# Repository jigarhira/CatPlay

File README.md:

# CatPlay
#### Device that allows you to play with your cat from anywhere.
CatPlay is a system comprised of an adjustable laser module and a live video stream. The user is shown a live video stream and can use controls on their mobile device to manipulate the laser pointer and play with the cat.

## Hardware
Laser Module is mounted on two servo motors to adjust laser position. Camera module is used to capture live stream. All components are connected to a Raspberry Pi Zero W which hosts the web server for the application.

## Software
When a client connects to the web server, they are provided with a video stream and control buttons to manipulate the laser in real time.

#
#### (project is a work in progress)

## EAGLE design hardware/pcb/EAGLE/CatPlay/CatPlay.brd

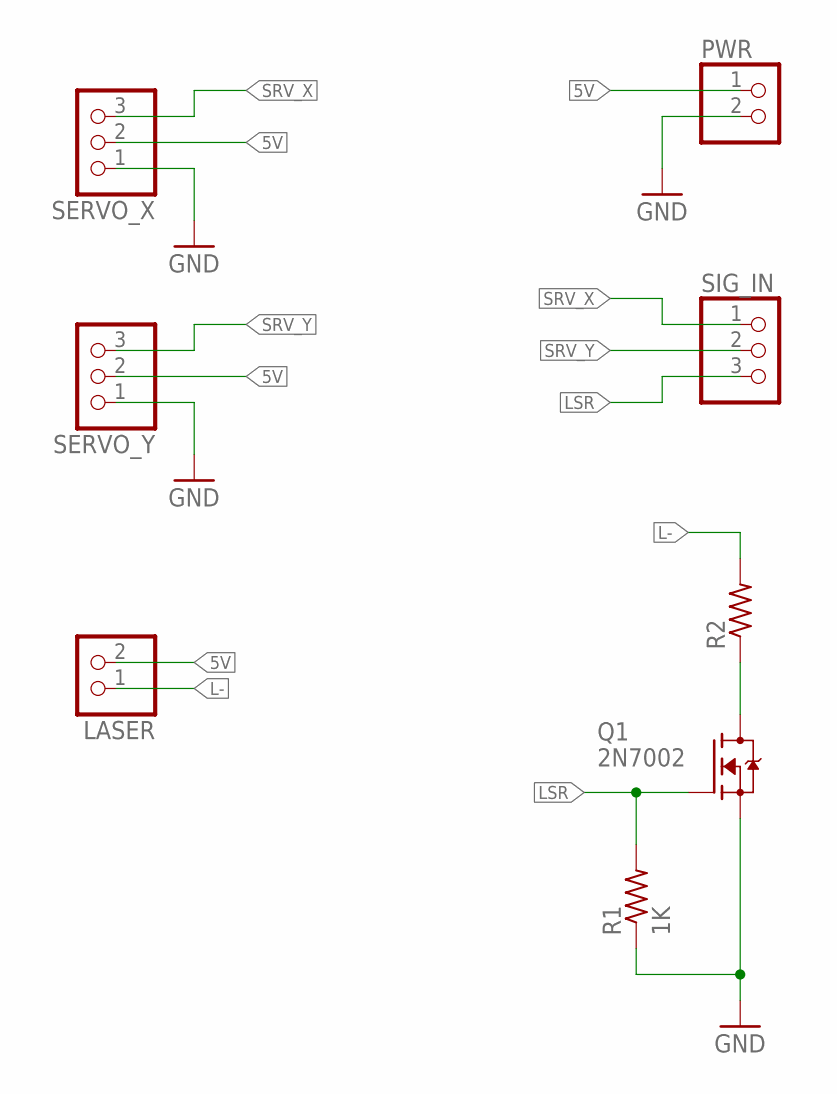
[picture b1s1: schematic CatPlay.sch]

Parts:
LASER: PINHD-1X2; 1X02
PWR: PINHD-1X2; 1X02
Q1: 2N7002; SOT-23
R1: 1K; R0603
R2: R-US_R0603; R0603
SERVO_X: PINHD-1X3; 1X03
SERVO_Y: PINHD-1X3; 1X03
SIG_IN: PINHD-1X3; 1X03

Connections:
5V: LASER.2, PWR.1, SERVO_X.2, SERVO_Y.2
GND: PWR.2, Q1.2 (S), R1.1, SERVO_X.1, SERVO_Y.1
L-: LASER.1, R2.2
LSR: Q1.1 (G), R1.2, SIG_IN.3
unnamed: Q1.3 (D), R2.1
SRV_X: SERVO_X.3, SIG_IN.1
SRV_Y: SERVO_Y.3, SIG_IN.2

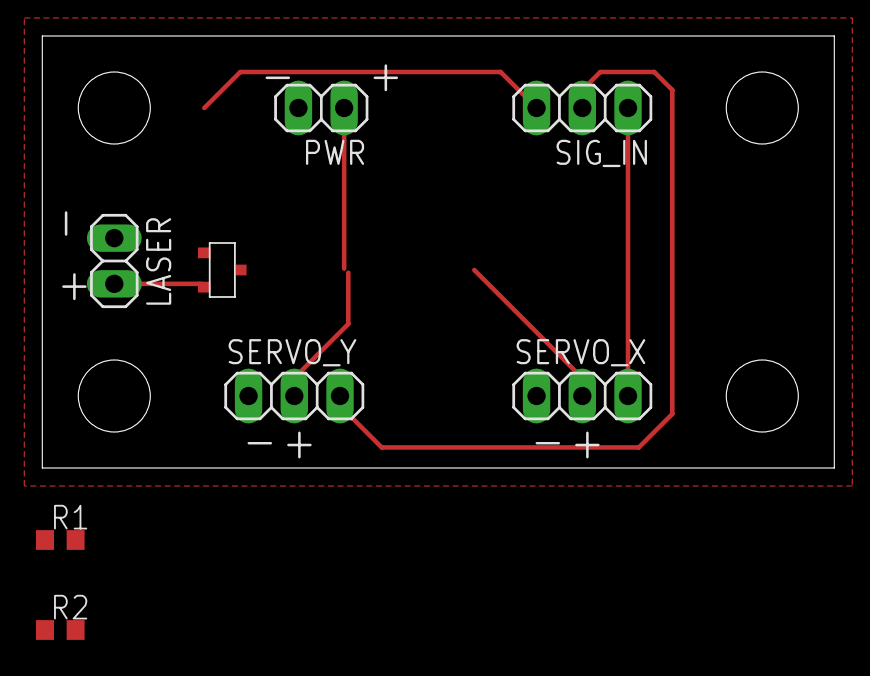
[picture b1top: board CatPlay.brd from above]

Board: 2 copper layers, 44.0 x 24.0 mm, 8 parts (0 on the bottom side), 7 nets.

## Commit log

2019-06-29 updated .gitignore for pycharm files
2019-06-29 Added file structure for server
2019-06-29 added text file in client for clarity
2019-07-01 Added ffmpeg piping
2019-09-30 added hardware folder
2019-09-30 Added servo class
2019-10-01 Added HTTP Server handling example
2020-02-09 updated pcb and gitignore
2020-05-21 clean for jira [CAT-18]
2020-05-22 Updated BOM [CAT-7]
2020-05-22 Updated Schematic [CAT-4]
2020-05-29 added raspimjepg binary CAT-10
